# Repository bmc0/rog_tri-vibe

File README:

SMD runoffgroove.com Tri-Vibe modified for better PSRR and less LFO
bleed-through.

License:
  All files contained in this repository are released under the same license
  as the original Tri-Vibe: CC BY-NC-SA 3.0. PCB design copyright (c)
  Michael Barbour, 2021. Original circuit by runoffgroove.com.

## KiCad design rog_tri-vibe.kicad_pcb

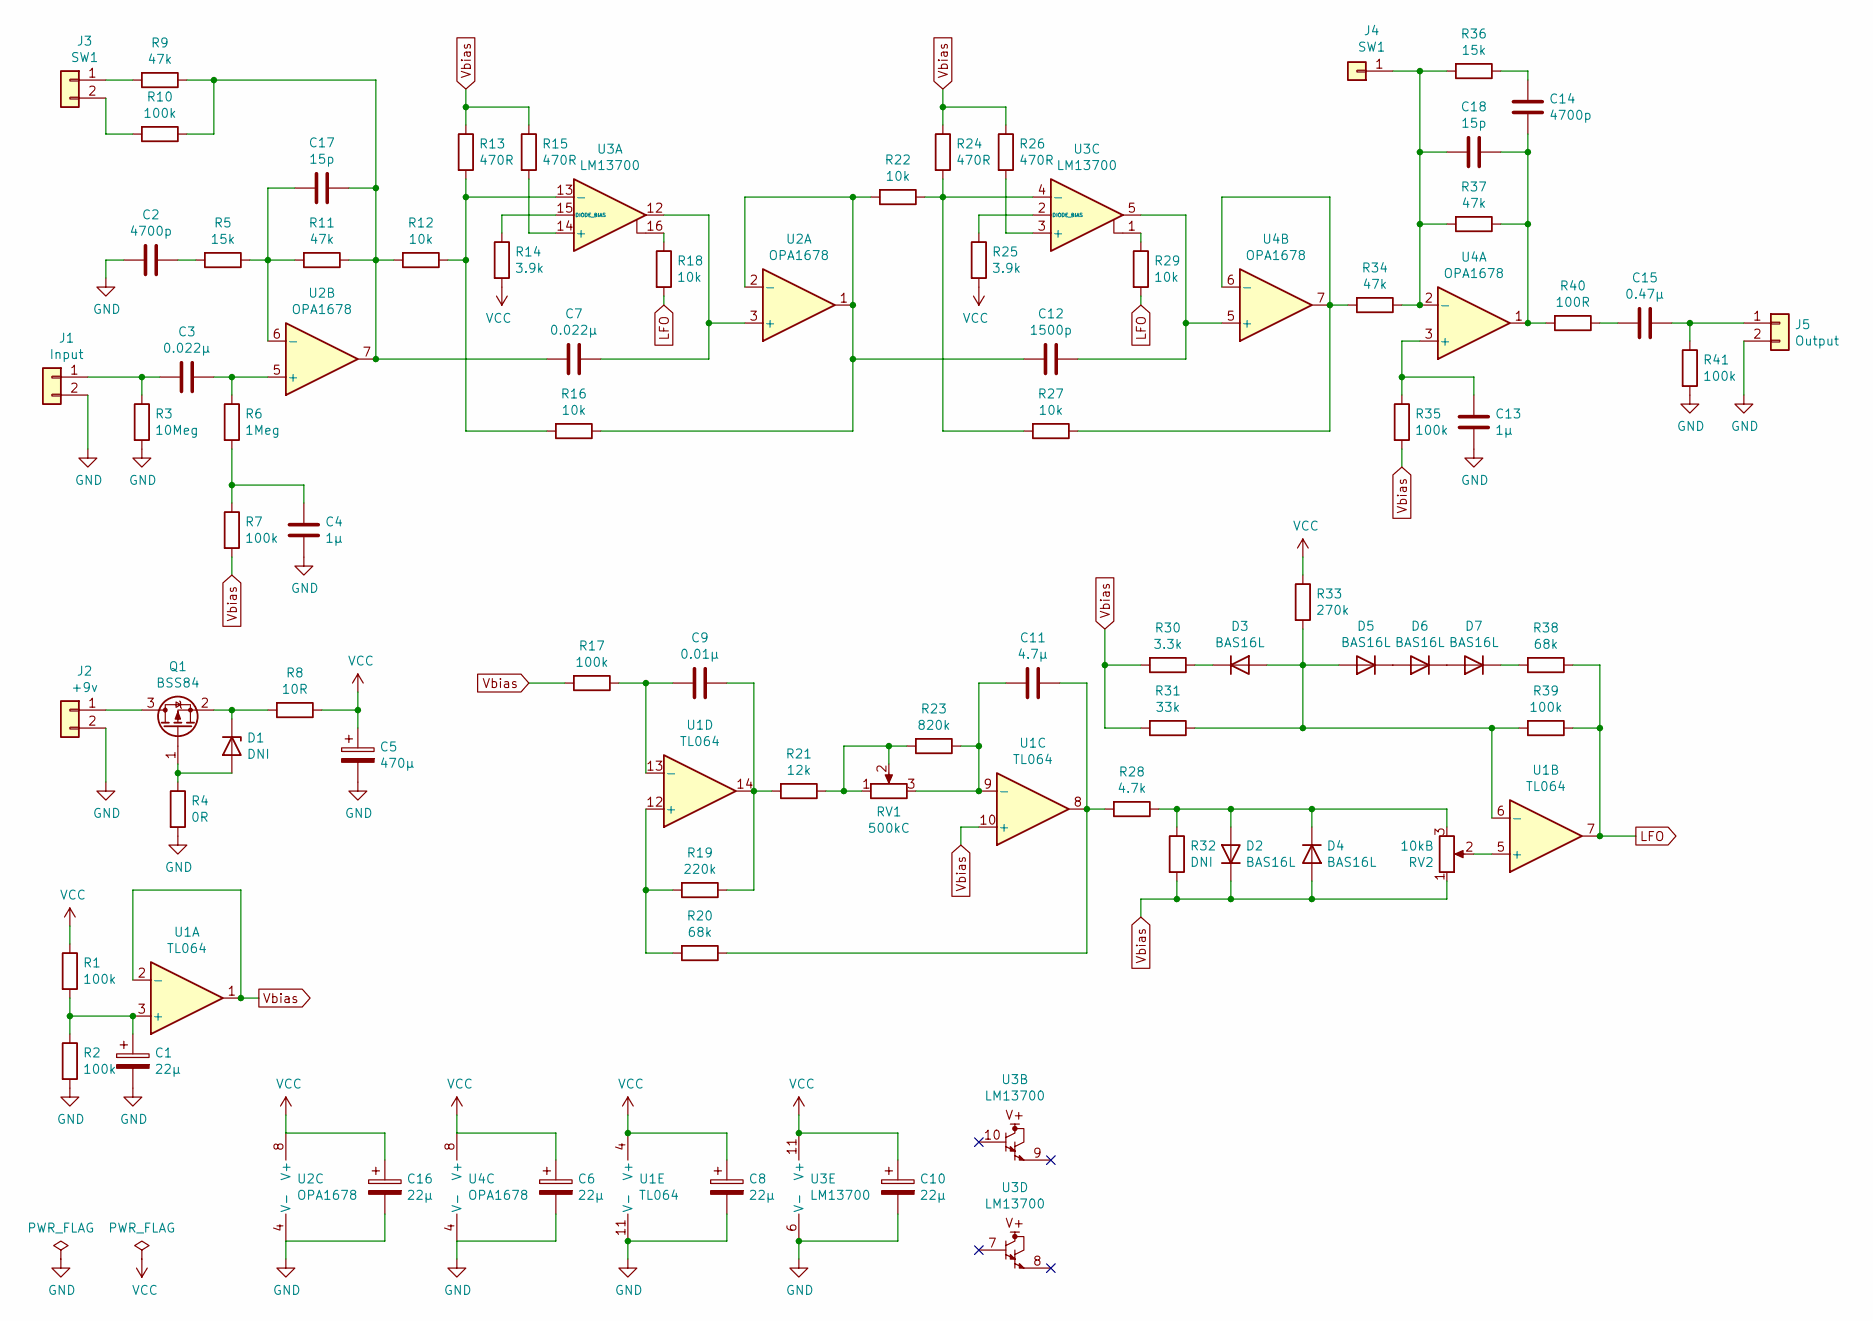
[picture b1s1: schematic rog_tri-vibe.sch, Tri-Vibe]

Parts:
C1, C6, C8, C10, C16: 22µ; CP_Radial_D5.0mm_P2.00mm
C2, C14: 4700p; C_0603_1608Metric
C3, C7: 0.022µ; C_Rect_L7.2mm_W2.5mm_P5.00mm_FKS2_FKP2_MKS2_MKP2
C4, C13: 1µ; C_0603_1608Metric
C5: 470µ; CP_Radial_D10.0mm_P5.00mm
C9: 0.01µ; C_0603_1608Metric
C11: 4.7µ; C_Radial_D5.0mm_H5.0mm_P2.00mm
C12: 1500p; C_0603_1608Metric
C15: 0.47µ; C_Rect_L7.2mm_W4.5mm_P5.00mm_FKS2_FKP2_MKS2_MKP2
C17, C18: 15p; C_0603_1608Metric
D1: DNI; D_SOT-23_ANK
D2, D3, D4, D5, D6, D7: BAS16L; D_SOT-23_ANK
J1: Input; SolderWire-0.5sqmm_1x02_P4.6mm_D0.9mm_OD2.1mm
J2: +9v; SolderWire-0.5sqmm_1x02_P4.6mm_D0.9mm_OD2.1mm
J3: SW1; SolderWire-0.5sqmm_1x02_P4.6mm_D0.9mm_OD2.1mm
J4: SW1; SolderWire-0.5sqmm_1x01_D0.9mm_OD2.1mm
J5: Output; SolderWire-0.5sqmm_1x02_P4.6mm_D0.9mm_OD2.1mm
Q1: BSS84; SOT-23
R1, R2, R7, R10, R17, R35, R39, R41: 100k; R_0603_1608Metric
R3: 10Meg; R_0603_1608Metric
R4: 0R; R_0603_1608Metric
R5, R36: 15k; R_0603_1608Metric
R6: 1Meg; R_0603_1608Metric
R8: 10R; R_0805_2012Metric
R9, R11, R34, R37: 47k; R_0603_1608Metric
R12, R16, R18, R22, R27, R29: 10k; R_0603_1608Metric
R13, R15, R24, R26: 470R; R_0603_1608Metric
R14, R25: 3.9k; R_0603_1608Metric
R19: 220k; R_0603_1608Metric
R20, R38: 68k; R_0603_1608Metric
R21: 12k; R_0603_1608Metric
R23: 820k; R_0603_1608Metric
R28: 4.7k; R_0603_1608Metric
R30: 3.3k; R_0603_1608Metric
R31: 33k; R_0603_1608Metric
R32: DNI; R_0603_1608Metric
R33: 270k; R_0603_1608Metric
R40: 100R; R_0603_1608Metric
RV1: 500kC; 16mm_potentiometer_rear
RV2: 10kB; 16mm_potentiometer_rear
U1: TL064; SOIC-14_3.9x8.7mm_P1.27mm
U2, U4: OPA1678; SOIC-8_3.9x4.9mm_P1.27mm
U3: LM13700; SOIC-16_3.9x9.9mm_P1.27mm

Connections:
GND: C1.2, C2.2, C4.2, C5.2, C6.2, C8.2, C10.2, C13.2, C16.2, J1.2, J2.2, J5.2, R2.2, R3.2, R4.2, R41.2, U1.11 (V-), U2.4 (V-), U3.6 (V-), U4.4 (V-)
LFO: R18.2, R29.2, R38.1, R39.1, U1.7
unnamed: C1.1, R1.2, R2.1, U1.3 (+)
unnamed: C2.1, R5.2
unnamed: C3.1, R6.1, U2.5 (+)
unnamed: C3.2, J1.1, R3.1
unnamed: C4.1, R6.2, R7.1
unnamed: C7.1, U2.3 (+), U3.12
unnamed: C9.1, R19.1, R21.2, U1.14
unnamed: C9.2, R17.1, U1.13 (-)
unnamed: C11.1, R20.1, R28.2, U1.8
unnamed: C11.2, R23.1, RV1.3, U1.9 (-)
unnamed: C12.1, U3.5, U4.5 (+)
unnamed: C12.2, R16.1, R22.2, U2.1, U2.2 (-)
unnamed: C13.1, R35.1, U4.3 (+)
unnamed: C14.1, R36.1
unnamed: C14.2, C18.1, R37.1, R40.2, U4.1
unnamed: C15.1, J5.1, R41.1
unnamed: C15.2, R40.1
unnamed: C7.2, C17.1, R9.1, R10.1, R11.1, R12.2, U2.7
unnamed: C17.2, R5.1, R11.2, U2.6 (-)
unnamed: C18.2, J4.1, R34.1, R36.2, R37.2, U4.2 (-)
unnamed: D1.1 (K), Q1.2 (S), R8.2
unnamed: D1.2 (A), Q1.1 (G), R4.1
unnamed: D2.2 (A), D4.1 (K), R28.1, R32.1, RV2.3
unnamed: D3.1 (K), R30.1
unnamed: D3.2 (A), D5.2 (A), R31.1, R33.2, R39.2, U1.6 (-)
unnamed: D5.1 (K), D6.2 (A)
unnamed: D6.1 (K), D7.2 (A)
unnamed: D7.1 (K), R38.2
unnamed: J2.1, Q1.3 (D)
unnamed: J3.1, R9.2
unnamed: J3.2, R10.2
unnamed: R12.1, R13.2, R16.2, U3.13 (-)
unnamed: R14.1, U3.15 (DIODE_BIAS)
unnamed: R15.2, U3.14 (+)
unnamed: R18.1, U3.16
unnamed: R19.2, R20.2, U1.12 (+)
unnamed: R21.1, R23.2, RV1.1, RV1.2
unnamed: R22.1, R24.2, R27.2, U3.4 (-)
unnamed: R25.1, U3.2 (DIODE_BIAS)
unnamed: R26.2, U3.3 (+)
unnamed: R27.1, R34.2, U4.6 (-), U4.7
unnamed: R29.1, U3.1
unnamed: RV2.2, U1.5 (+)
VCC: C5.1, C6.1, C8.1, C10.1, C16.1, R1.1, R8.1, R14.2, R25.2, R33.1, U1.4 (V+), U2.8 (V+), U3.11 (V+), U4.8 (V+)
Vbias: D2.1 (K), D4.2 (A), R7.2, R13.1, R15.1, R17.2, R24.1, R26.1, R30.2, R31.2, R32.2, R35.2, RV2.1, U1.1, U1.2 (-), U1.10 (+)

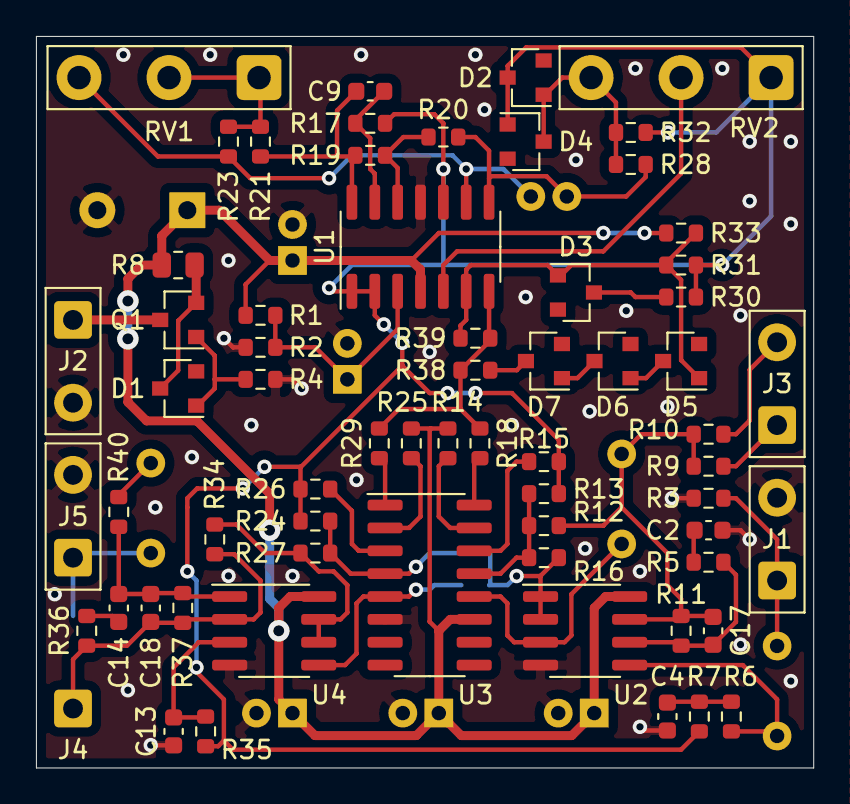
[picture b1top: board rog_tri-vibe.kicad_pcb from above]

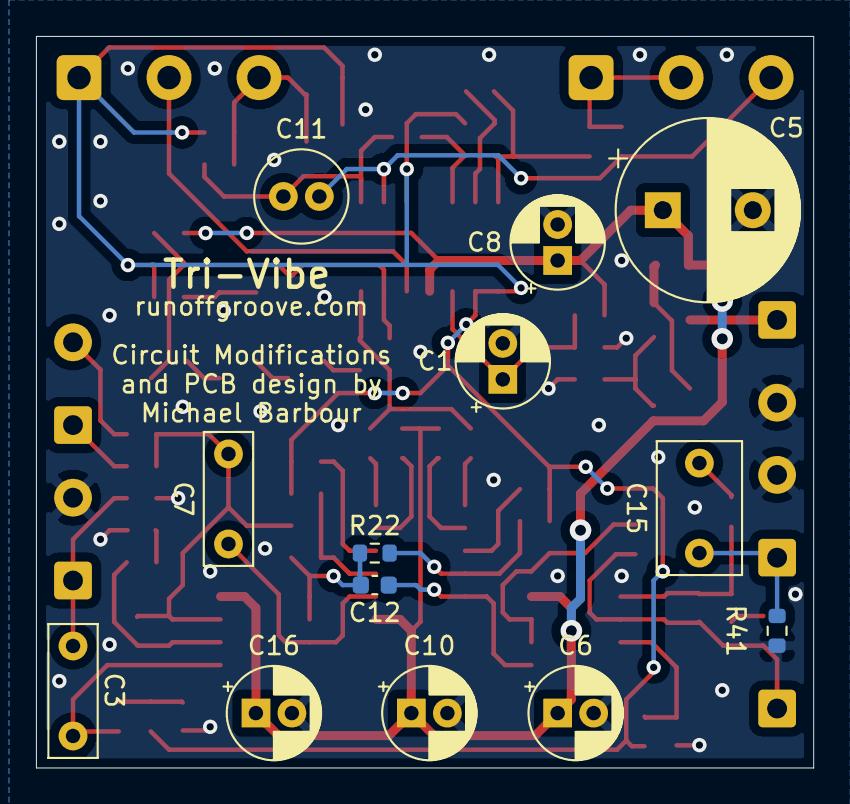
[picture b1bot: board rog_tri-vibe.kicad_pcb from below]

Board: 2 copper layers, 43.2 x 40.6 mm, 78 parts (13 on the bottom side), 47 nets.

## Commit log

2021-05-12 Initial commit.
